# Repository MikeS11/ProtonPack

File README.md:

[![Contributors][contributors-shield]][contributors-url]
[![Forks][forks-shield]][forks-url]
[![Stargazers][stars-shield]][stars-url]
[![Issues][issues-shield]][issues-url]
[![MIT License][license-shield]][license-url]
[![Twitter][Twitter-shield]][Twitter-url]

<!-- PROJECT LOGO -->
<br />
<p align="center">

  <h3 align="center">GhostKitty Proton Pack</h3>

  <p align="center">
  This is my contribution to the GB community. This project adds a bit more movie / game accuracy but also a little fun :)

<!-- TABLE OF CONTENTS -->
## Table of Contents

* [About the Project](#about-the-project)
  * [Built With](#Build-Requirements)
* [Getting Started](#getting-started)
  * [Prerequisites](#prerequisites)
  * [Wand Configuration](#wand-configuration)  
* [License](#license)
* [Contact](#contact)
* [Acknowledgements](#acknowledgements)

<!-- ABOUT THE PROJECT -->
## About The Project

<div align="center">
  YouTube Video<br /> 

Original Prototype <br />
</p>

Afterlife Cyclotron 40 segment LED ring<br /> 
</p>
</div>

I want this to be a source for anyone to use to create their own proton pack kits for as cheap as possible and still include all the features for a rumble motor, 2 firing mechanisms, all functioning LEDs in the wand, pack themes, full 28 segment bar graph, and an output for a vent kit.

**Current Themes for the pack:**
*  Movie
*  Stasis / Afterlife 
*  Slime
*  Meson
*  Christmas!
*  *Future* Halloween

### Getting Started

### Build Requirements:

*  1 - Arduino Nano (Amazon)  
*  1 - DFPlayer Mini (Be aware that some of the knock offs do not perform correctly, reference to the busy pin may not work) (Digikey Only)
*  1 - Any amplifing circuit (Currently testing an Adafruit Stereo 20W Class D Audio Amplifier - MAX9744)  (Amazon, Digikey)
*  1 - LED Matrix Driver - HT16K33 Breakout (for the bar graph) (Amazon, Digikey)
*  1 - 28 segment bargraph (barmeter.com, ebay is your best option)
*  1 - Pack of neopixels or equivalent WS2812B ( Vent and wand LEDs) (Amazon)
*  1 - LED strip (Powercell)  (Amazon)
*  1 - Adafruit Jewel - Wand Tip (WAs looking at the Pixie but there is a concern of its overhead requirements when working with normal WS2812B's, and they can not be chained together with WS2812B's) (Amazon, Digikey)
*  1 - 40 Segment LED ring or LED strip (WS2812B's) - Afterlife Cyclotron LED
*  Pack of 24 awg stranded cable (Amazon) - To keep things clean you might want to look at ribbon cables or multi conductor cables. 
*  For circuit noise filtering, I would add a 1000uF electrolytic capacitors closes to the neopixels, and a 470 Ohm resistor before the first led of the strip (This is recommended by Adafruit as well). I would recommend one 1000uF capacitor for the wand to filter out noise from both the bargraph and the neopixels. (See Diagram)
*  If you are printing the PCB you will need a RJ45 Connector, 2.54mm JST Connectors, 2.54mm Dupont Connectors, 1 MP1584EN Buck Converter, 7805 Voltage regulator, 2 1k Ohm resistors, and some 0.1 uF and 0.33 uF ceramic capacitors. Additionally for the wand, 1000uF capacitor, a 1N4001 diode and a transistor.

### Prerequisites

You are going to need to install the following libraries:

**For the Audio DFPlayer Player:**
*  SoftwareSerial.h
*  DFPlayerMini_Fast.h

**For the WS2812B / NeoPixel LEDs**
*  Adafruit_NeoPixel.h

**Custom Libraries for the Powercell / Cyclotron / Bargraph Animiations**
*  GBLEDPatternsJewel.h
*  BGSequence.h

**Sound Files for the DFPlayer or Alternative Player**

<a href="https://mega.nz/file/R5sWzCha#zm4DIskyvmF08JNp8MnOAEqCDmNe2MSCN6wtFMExKlU">Here are some sound files I found online or mixed myself</a>

### Wand Configuration

<!-- CONTRIBUTING -->
## Contributing

Contributions are what make the open source community such an amazing place to be learn, inspire, and create. Any contributions you make are **greatly appreciated**.

1. Fork the Project
2. Create your Feature Branch (`git checkout -b feature/AmazingFeature`)
3. Commit your Changes (`git commit -m 'Add some AmazingFeature'`)
4. Push to the Branch (`git push origin feature/AmazingFeature`)
5. Open a Pull Request

<!-- LICENSE -->
## License

Distributed under the MIT License. See `LICENSE` for more information.

<!-- CONTACT -->
## Contact

Mike Simone - [@mikesimone3](https://twitter.com/mikesimone3) 

Project Link: [https://github.com/MikeS11/ProtonPack](https://github.com/MikeS11/ProtonPack)

<!-- ACKNOWLEDGEMENTS -->
## Acknowledgements

*  Eric Banker for the for the wonder work completed on his Arduino project. (a couple of his functions are referenced in this project) 
* 
* 

<!-- MARKDOWN LINKS & IMAGES -->
<!-- https://www.markdownguide.org/basic-syntax/#reference-style-links -->
[contributors-shield]: https://img.shields.io/github/contributors/MikeS11/ProtonPack.svg?style=flat-square
[contributors-url]: https://github.com/MikeS11/ProtonPack/graphs/contributors
[forks-shield]: https://img.shields.io/github/forks/MikeS11/ProtonPack.svg?style=flat-square
[forks-url]: https://github.com/MikeS11/ProtonPack/network/members
[stars-shield]: https://img.shields.io/github/stars/MikeS11/ProtonPack.svg?style=flat-square
[stars-url]: https://github.com/MikeS11/ProtonPack/stargazers
[issues-shield]: https://img.shields.io/github/issues/MikeS11/ProtonPack.svg?style=flat-square
[issues-url]: https://github.com/MikeS11/ProtonPack/issues
[license-shield]: https://img.shields.io/github/license/MikeS11/ProtonPack.svg?style=flat-square
[license-url]: https://github.com/MikeS11/ProtonPack/blob/master/LICENSE.txt
[twitter-shield]: https://img.shields.io/badge/-Twitter-black.svg?style=flat-square&logo=Twitter&colorB=555
[twitter-url]: https://Twitter.com/mikesimone3
[product-screenshot]: images/screenshot.png

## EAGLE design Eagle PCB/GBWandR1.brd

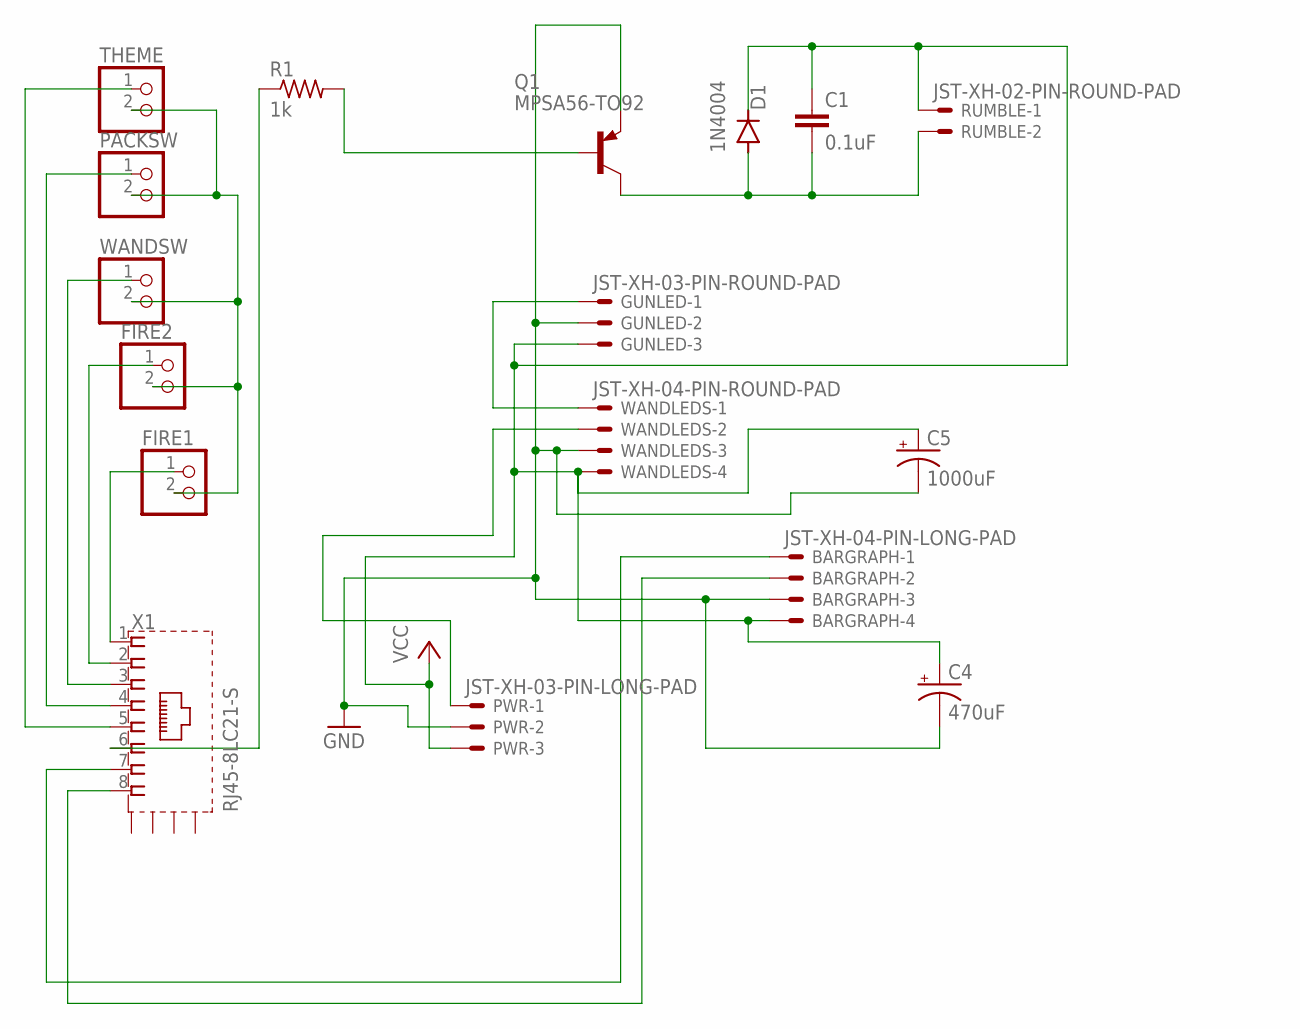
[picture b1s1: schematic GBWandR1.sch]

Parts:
BARGRAPH: JST-XH-04-PIN-LONG-PAD; JST-XH-04-PACKAGE-LONG-PAD
C1: 0.1uF; C050-024X044
C4: 470uF; E3,5-8
C5: 1000uF; E3,5-8
D1: 1N4004; DO41-10
FIRE1, FIRE2: PINHD-1X2; 1X02
GUNLED: JST-XH-03-PIN-ROUND-PAD; JST-XH-03-PACKAGE-ROUND-PAD
PACKSW: PINHD-1X2; 1X02
PWR: JST-XH-03-PIN-LONG-PAD; JST-XH-03-PACKAGE-LONG-PAD
Q1: MPSA56-TO92; TO92-CBE
R1: 1k; 0207/9
RUMBLE: JST-XH-02-PIN-ROUND-PAD; JST-XH-02-PACKAGE-ROUND-PAD
THEME: PINHD-1X2; 1X02
WANDLEDS: JST-XH-04-PIN-ROUND-PAD; JST-XH-04-PACKAGE-ROUND-PAD
WANDSW: PINHD-1X2; 1X02
X1: RJ45-8LC21-S; RJ45-SHIELD1

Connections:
GND: BARGRAPH.3, C4.-, C5.-, GUNLED.2, PWR.2, Q1.E, WANDLEDS.3
unnamed: PWR.1, WANDLEDS.2
unnamed: FIRE1.1, X1.1
unnamed: FIRE2.1, X1.2
unnamed: WANDSW.1, X1.3
unnamed: PACKSW.1, X1.4
unnamed: THEME.1, X1.5
unnamed: GUNLED.1, WANDLEDS.1
unnamed: FIRE1.2, FIRE2.2, PACKSW.2, THEME.2, WANDSW.2
unnamed: R1.1, X1.6
unnamed: Q1.B, R1.2
unnamed: BARGRAPH.2, X1.8
unnamed: BARGRAPH.1, X1.7
unnamed: C1.2, D1.A, Q1.C, RUMBLE.2
VCC: BARGRAPH.4, C1.1, C4.+, C5.+, D1.C, GUNLED.3, PWR.3, RUMBLE.1, WANDLEDS.4

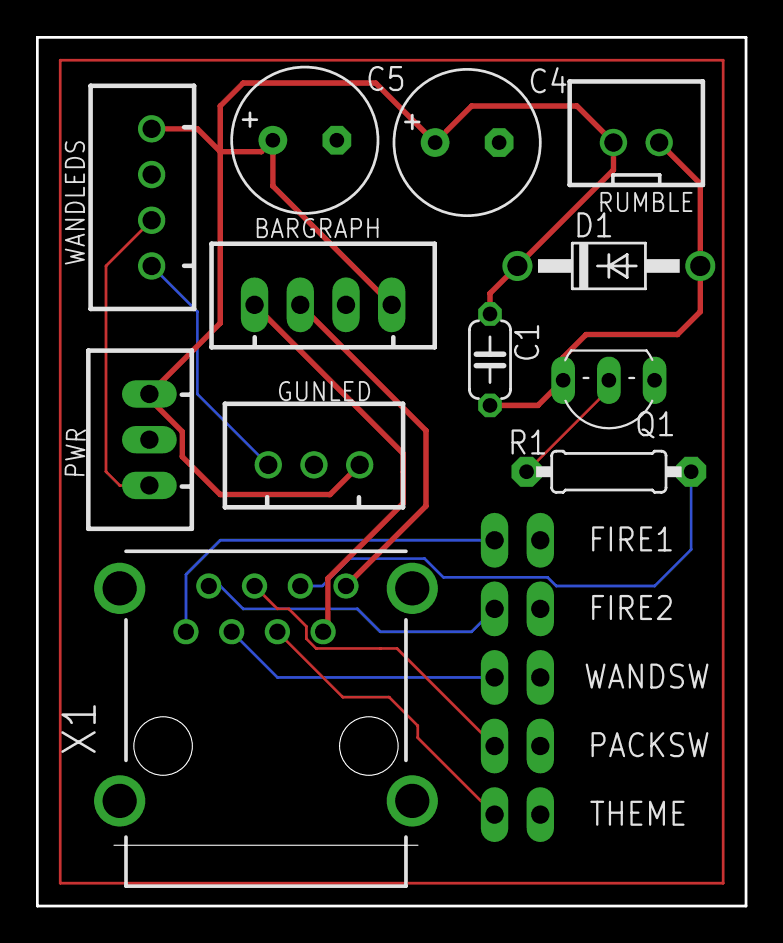
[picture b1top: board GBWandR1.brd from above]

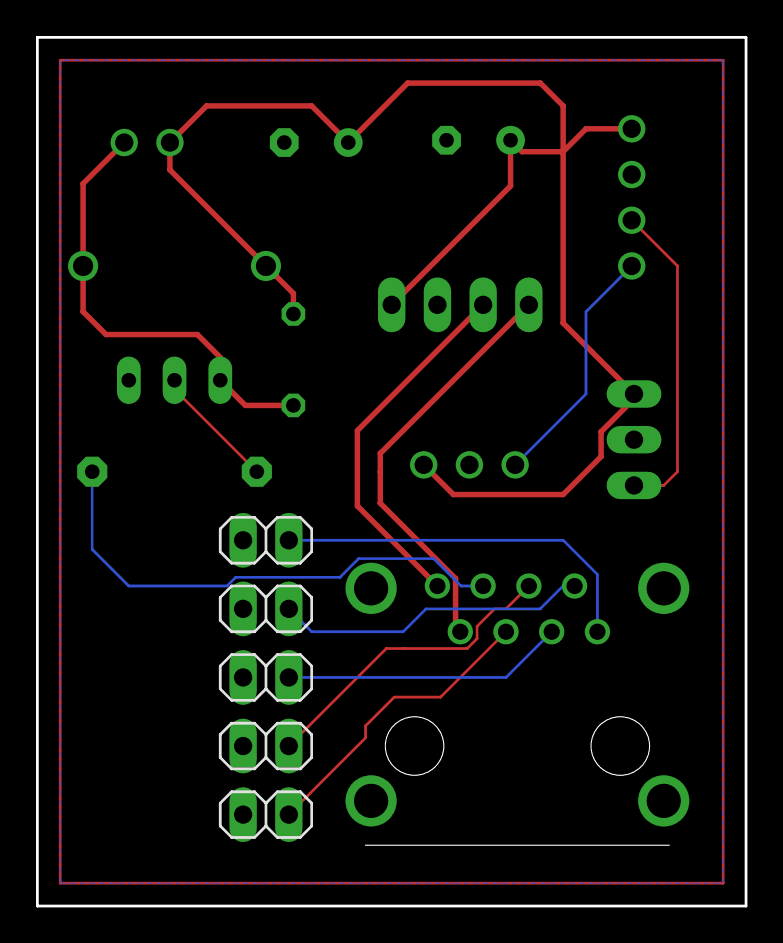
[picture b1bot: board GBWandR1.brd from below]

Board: 2 copper layers, 39.4 x 48.3 mm, 17 parts (5 on the bottom side), 15 nets.

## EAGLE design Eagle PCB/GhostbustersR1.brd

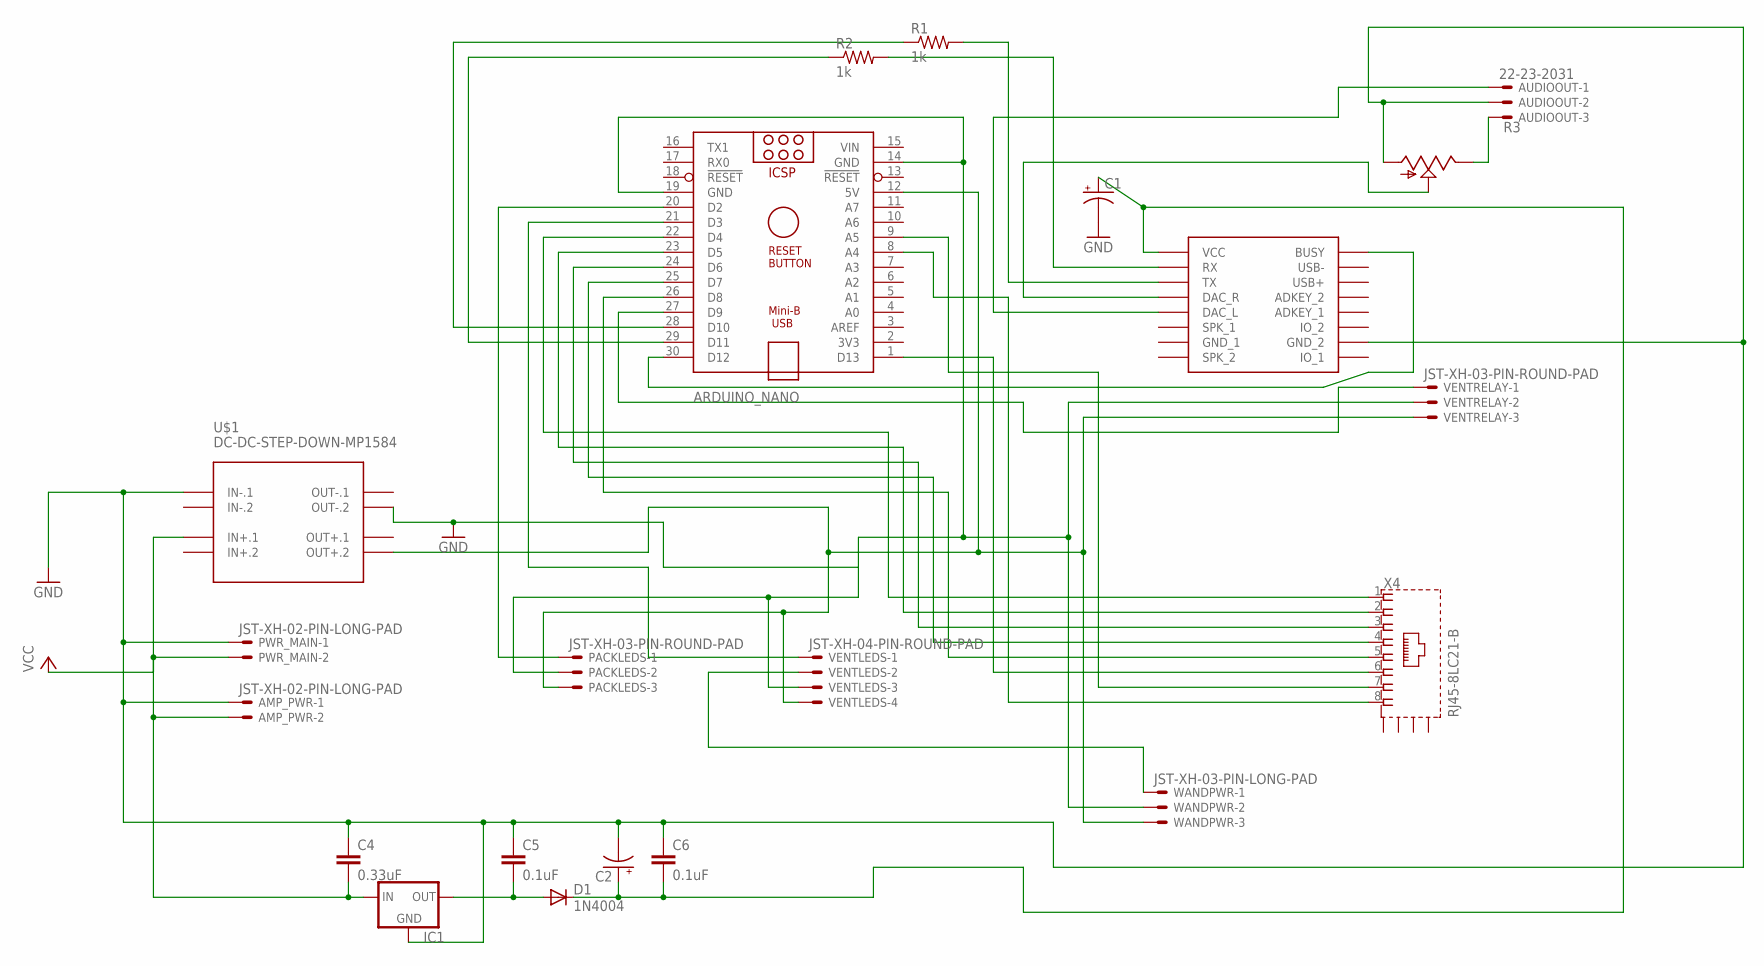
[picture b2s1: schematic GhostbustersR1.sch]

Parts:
AMP_PWR: JST-XH-02-PIN-LONG-PAD; JST-XH-02-PACKAGE-LONG-PAD
ARDUINO_NANO: ARDUINO_NANO
AUDIOOUT: 22-23-2031
C1, C2: CPOL-USE3.5-8; E3,5-8
C4: 0.33uF; C2.5-4
C5, C6: 0.1uF; C2.5-4
D1: 1N4004; DO41-10
DFPLAYER: DFPLAYER
IC1: 78MXXS
PACKLEDS: JST-XH-03-PIN-ROUND-PAD; JST-XH-03-PACKAGE-ROUND-PAD
PWR_MAIN: JST-XH-02-PIN-LONG-PAD; JST-XH-02-PACKAGE-LONG-PAD
R1, R2: 1k; 0207/12
R3: TRIM_US-B64Y; B64Y
U$1: DC-DC-STEP-DOWN-MP1584
VENTLEDS: JST-XH-04-PIN-ROUND-PAD; JST-XH-04-PACKAGE-ROUND-PAD
VENTRELAY: JST-XH-03-PIN-ROUND-PAD; JST-XH-03-PACKAGE-ROUND-PAD
WANDPWR: JST-XH-03-PIN-LONG-PAD; JST-XH-03-PACKAGE-LONG-PAD
X4: RJ45-8LC21-B; RJ45-SHIELD1

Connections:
GND: AMP_PWR.1, ARDUINO_NANO.14 (GND), ARDUINO_NANO.19 (GND), AUDIOOUT.2, C1.-, C2.-, C4.1, C5.1, C6.1, DFPLAYER.GND_2, IC1.GND, PACKLEDS.2, PWR_MAIN.1, R3.A, U$1.IN-.1, U$1.OUT-.2, VENTLEDS.3, VENTRELAY.2, WANDPWR.2
unnamed: ARDUINO_NANO.12 (5V), PACKLEDS.3, U$1.OUT+.2, VENTLEDS.4, VENTRELAY.3, WANDPWR.3
unnamed: ARDUINO_NANO.25 (D7), X4.4
unnamed: AUDIOOUT.3, R3.E
unnamed: ARDUINO_NANO.29 (D11), R2.1
unnamed: ARDUINO_NANO.28 (D10), R1.1
unnamed: ARDUINO_NANO.20 (D2), PACKLEDS.1
unnamed: ARDUINO_NANO.21 (D3), VENTLEDS.1
unnamed: VENTLEDS.2, WANDPWR.1
unnamed: ARDUINO_NANO.22 (D4), X4.1
unnamed: ARDUINO_NANO.23 (D5), X4.2
unnamed: ARDUINO_NANO.24 (D6), X4.3
unnamed: ARDUINO_NANO.26 (D8), X4.5
unnamed: ARDUINO_NANO.1 (D13), X4.6
unnamed: ARDUINO_NANO.30 (D12), DFPLAYER.BUSY
unnamed: DFPLAYER.DAC_R, R3.S
unnamed: AUDIOOUT.1, DFPLAYER.DAC_L
unnamed: ARDUINO_NANO.27 (D9), VENTRELAY.1
unnamed: ARDUINO_NANO.8 (A4), X4.8
unnamed: ARDUINO_NANO.9 (A5), X4.7
unnamed: DFPLAYER.TX, R1.2
unnamed: DFPLAYER.RX, R2.2
unnamed: C5.2, D1.A, IC1.OUT
unnamed: C1.+, C2.+, C6.2, D1.C, DFPLAYER.VCC
VCC: AMP_PWR.2, C4.2, IC1.IN, PWR_MAIN.2, U$1.IN+.1
VIN: ARDUINO_NANO.15 (VIN)

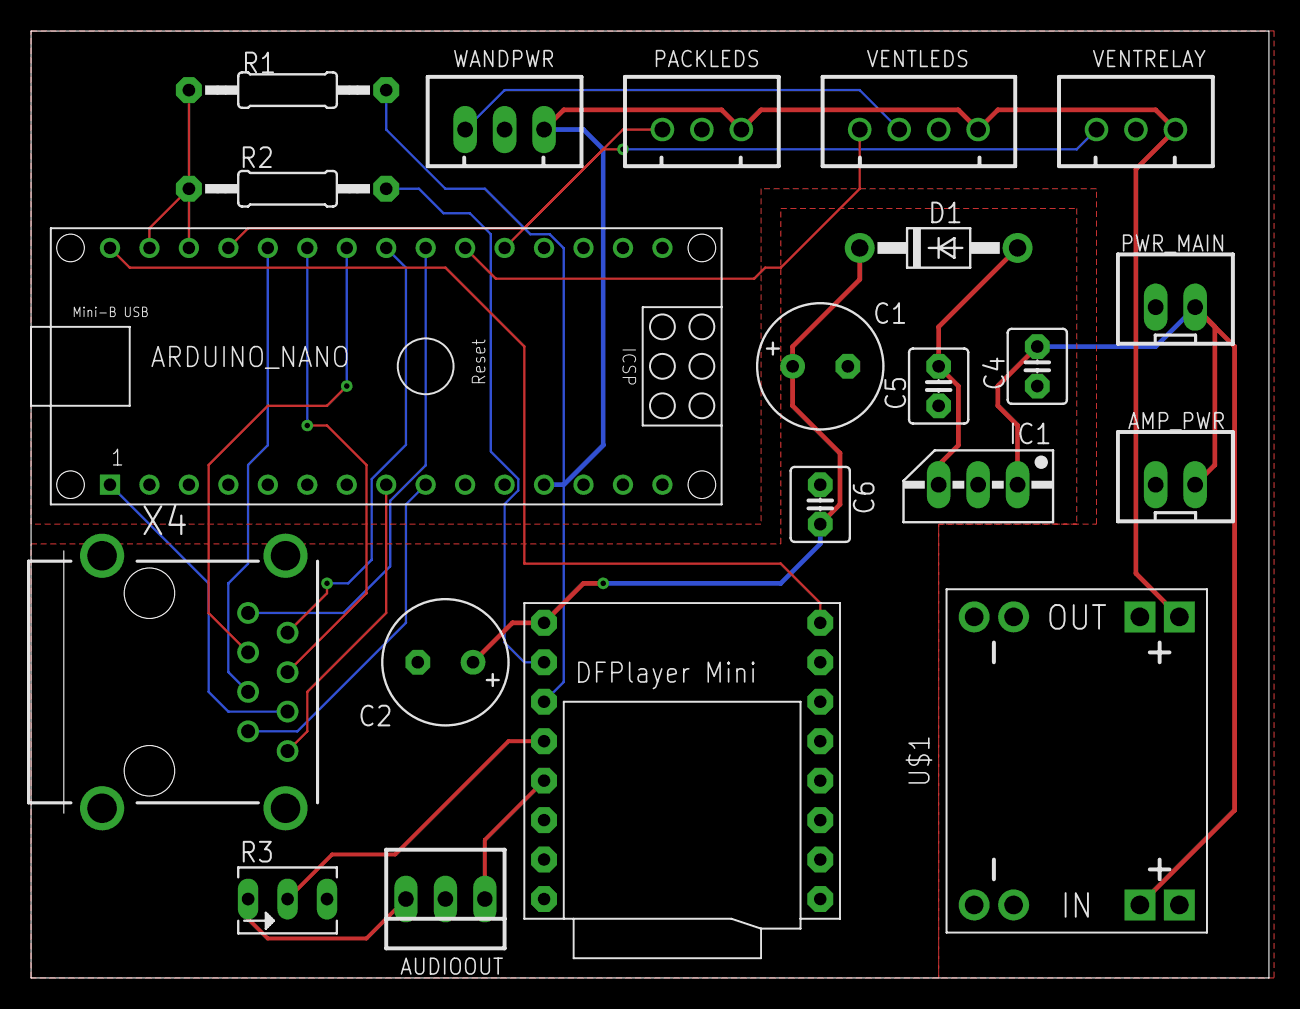
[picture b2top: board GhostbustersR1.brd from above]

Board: 2 copper layers, 79.7 x 60.9 mm, 21 parts (0 on the bottom side), 25 nets.

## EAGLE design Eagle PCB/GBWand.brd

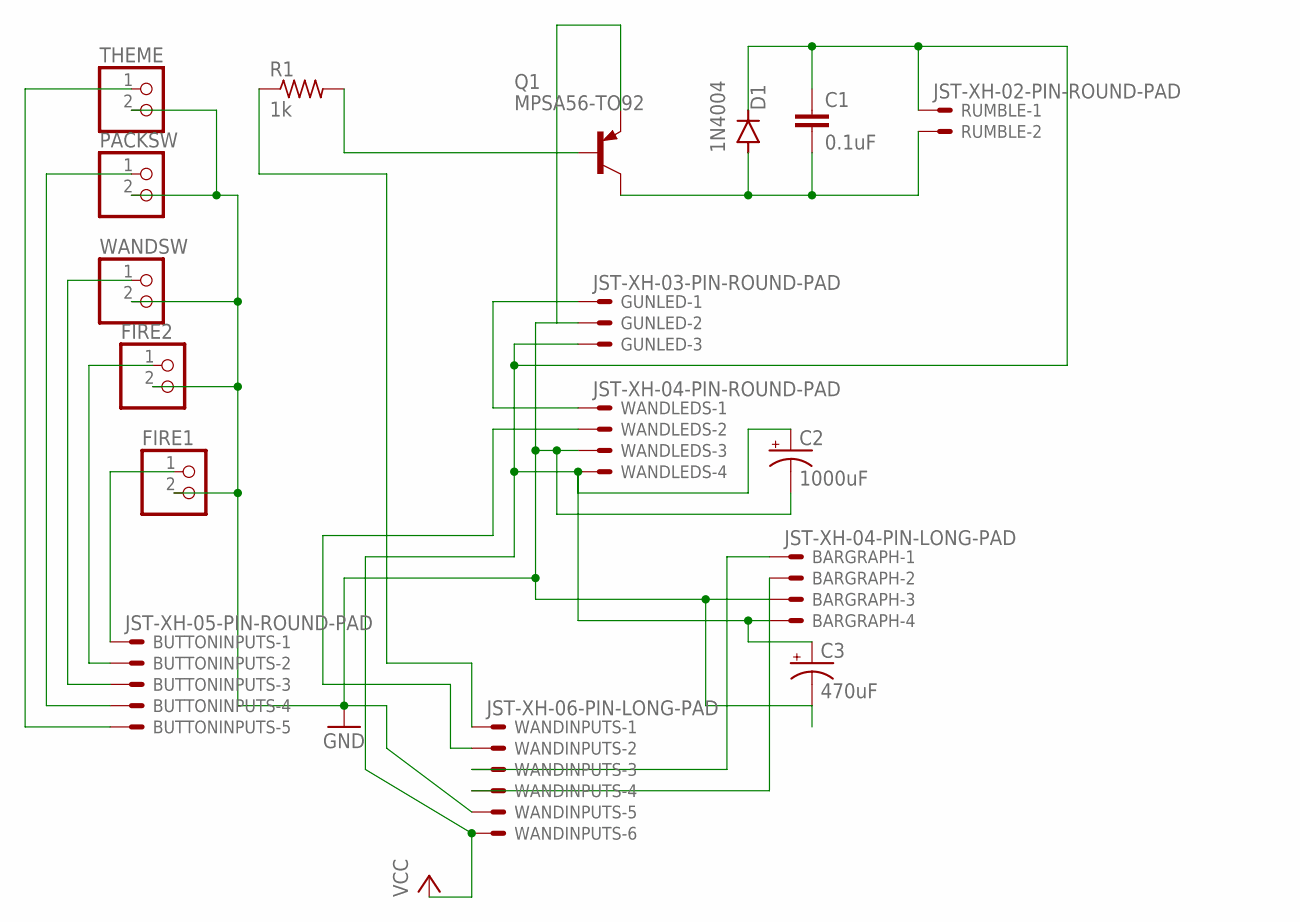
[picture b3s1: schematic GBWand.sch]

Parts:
BARGRAPH: JST-XH-04-PIN-LONG-PAD; JST-XH-04-PACKAGE-LONG-PAD
BUTTONINPUTS: JST-XH-05-PIN-ROUND-PAD; JST-XH-05-PACKAGE-ROUND-PAD
C1: 0.1uF; C050-024X044
C2: 1000uF; E2,5-6
C3: 470uF; E2,5-6
D1: 1N4004; DO41-10
FIRE1, FIRE2: PINHD-1X2; 1X02
GUNLED: JST-XH-03-PIN-ROUND-PAD; JST-XH-03-PACKAGE-ROUND-PAD
PACKSW: PINHD-1X2; 1X02
Q1: MPSA56-TO92; TO92-CBE
R1: 1k; 0207/9
RUMBLE: JST-XH-02-PIN-ROUND-PAD; JST-XH-02-PACKAGE-ROUND-PAD
THEME: PINHD-1X2; 1X02
WANDINPUTS: JST-XH-06-PIN-LONG-PAD; JST-XH-06-PACKAGE-LONG-PAD
WANDLEDS: JST-XH-04-PIN-ROUND-PAD; JST-XH-04-PACKAGE-ROUND-PAD
WANDSW: PINHD-1X2; 1X02

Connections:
GND: BARGRAPH.3, C2.-, C3.-, FIRE1.2, FIRE2.2, GUNLED.2, PACKSW.2, Q1.E, THEME.2, WANDINPUTS.5, WANDLEDS.3, WANDSW.2
unnamed: WANDINPUTS.2, WANDLEDS.2
unnamed: BUTTONINPUTS.1, FIRE1.1
unnamed: BUTTONINPUTS.2, FIRE2.1
unnamed: BUTTONINPUTS.3, WANDSW.1
unnamed: BUTTONINPUTS.4, PACKSW.1
unnamed: BUTTONINPUTS.5, THEME.1
unnamed: GUNLED.1, WANDLEDS.1
unnamed: R1.1, WANDINPUTS.1
unnamed: Q1.B, R1.2
unnamed: BARGRAPH.2, WANDINPUTS.4
unnamed: BARGRAPH.1, WANDINPUTS.3
unnamed: C1.2, D1.A, Q1.C, RUMBLE.2
VCC: BARGRAPH.4, C1.1, C2.+, C3.+, D1.C, GUNLED.3, RUMBLE.1, WANDINPUTS.6, WANDLEDS.4

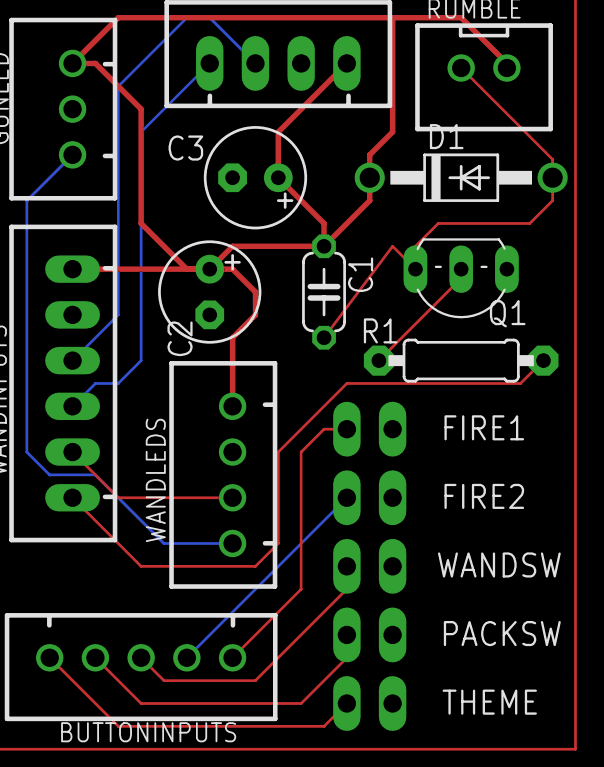
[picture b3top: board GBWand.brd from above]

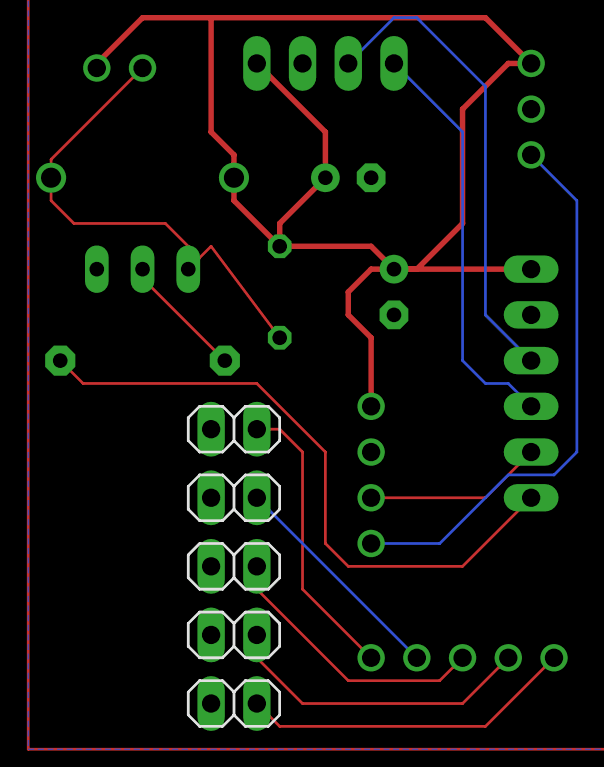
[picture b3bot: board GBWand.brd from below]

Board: 2 copper layers, 17 parts (5 on the bottom side), 14 nets.

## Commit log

2020-09-21 Version 1.0
    Version 1.0
2020-09-21 Updated Diagram
2020-09-21 Added for Bargraph Sequence LIbrary
2020-09-25 Untested PCBs
2021-11-08 Added Afterlife Source
    Added Afterlife Source
    Updated PCB, Ethernet port connector now on wand
2021-11-14 Added AL look and firing sequence sounds

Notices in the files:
parts and their libraries:
diy-modules: Released under the Creative Commons Attribution 4.0 International License: http://creativecommons.org/licenses/by/4.0
